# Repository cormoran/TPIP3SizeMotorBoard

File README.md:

# TPIP3SizeMotorBoard
ArduinoUnoCompatible Board for four wheel robot control (with TPIP3 image board)

[Document](https://cormoran.github.io/TPIP3SizeMotorBoard/)

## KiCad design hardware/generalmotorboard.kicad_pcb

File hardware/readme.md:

# 2016年度４号機向け モータ制御回路

## 機能

* ４つのモータを正転、逆転、停止、空転、速度調整
* ２つのサーボモータを制御
* 赤外線LED, 受信機
* 温度センサー
* 状態表示用LED 2つ
* VCC,GND出力付きアナログ入力対応汎用ポート 4つ （ガスセンサ等を接続可能）
* 汎用ディジタルIOポート 4つ（二つはスイッチとポート兼用）
* スイッチ入力 4つ（２つはIOポート兼用）
* Groveポート(I2C)
* シリアル通信ポート
* バッテリー電圧監視
* USBシリアル変換IC搭載、Arduino DEIによる書き込み対応
* USB給電・バッテリー給電自動切り替え（バッテリー優先）

など

一応2016年度 3号機向けだが、部内ロボコン等にも使用できるように色々付けてある

## 形状

* TPIP3の金属部分と完全に同じ大きさに設計
* ポートは全て横向きに設置することで高さを削減

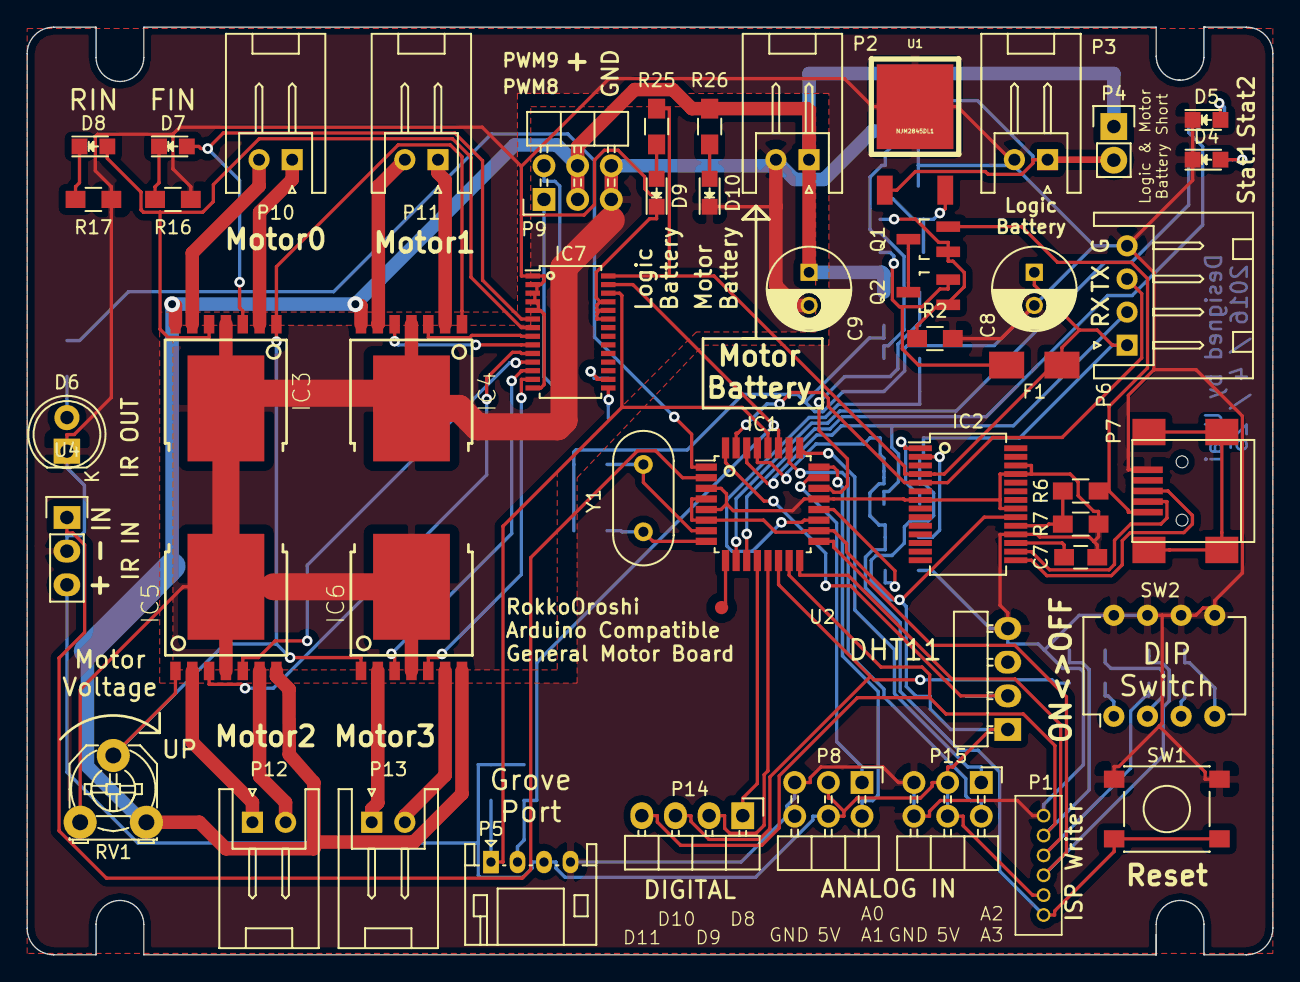
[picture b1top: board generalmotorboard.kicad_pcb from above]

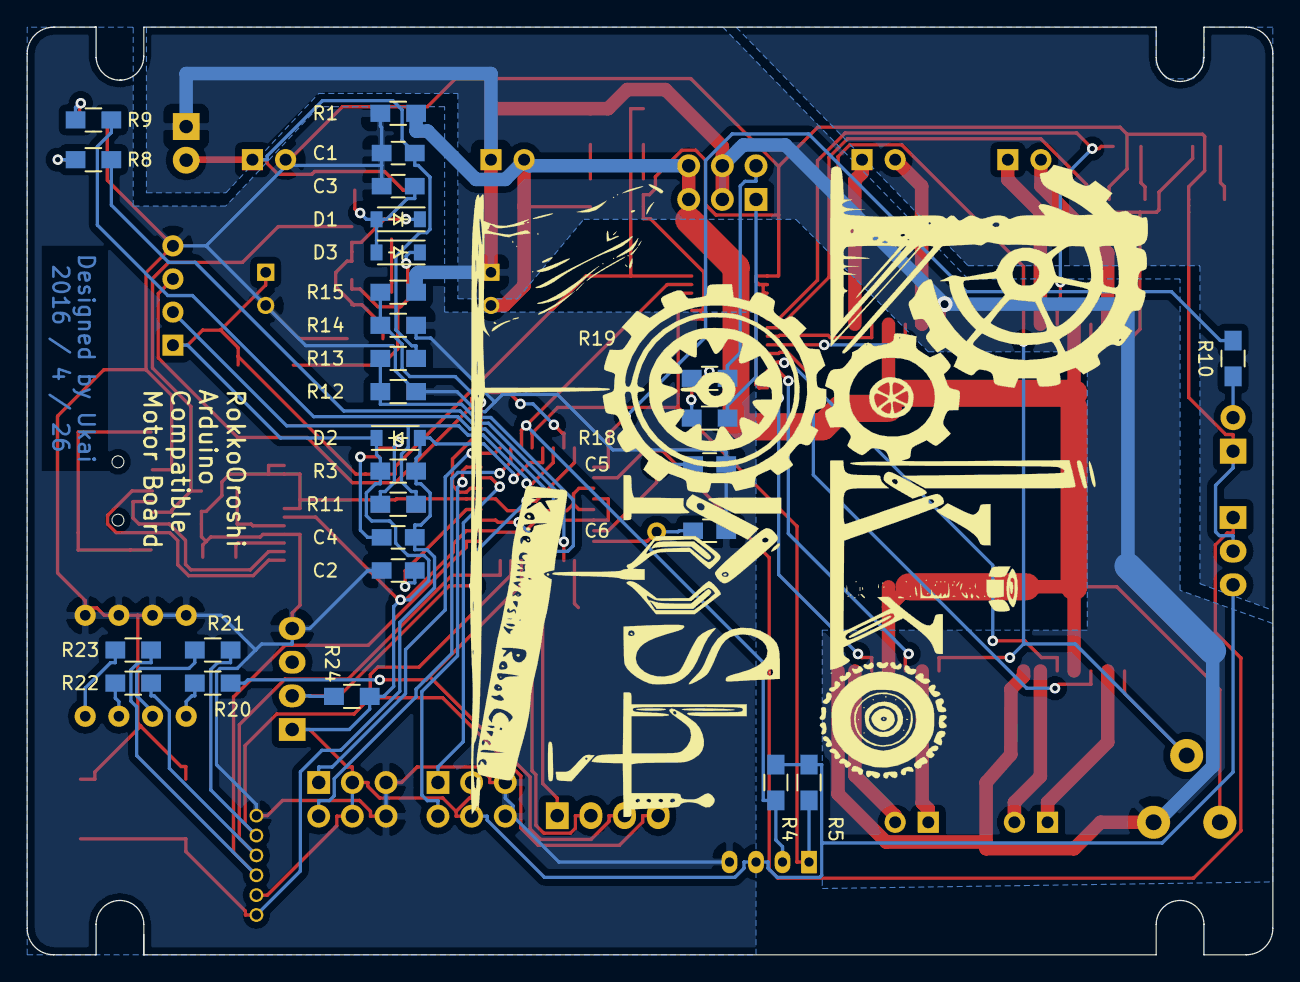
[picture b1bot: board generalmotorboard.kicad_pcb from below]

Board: 2 copper layers, 94.0 x 70.0 mm, 78 parts (28 on the bottom side), 74 nets.

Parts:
C1: 0.33uF; C_0805_HandSoldering
C2, C7: 100nF; C_0805_HandSoldering
C3: 2.2uF; C_0805_HandSoldering
C4: 0.1uF; C_0805_HandSoldering
C5, C6: 22pF; C_0805_HandSoldering
C8, C9: 470uF; C_Radial_D6.3_L11.2_P2.5
D1, D2, D3: D; SOD-123
D4: LED GREEN; LED_0805
D5: LED RED; LED_0805
D6: LED IR; LED-5MM
D7: Led FIN; LED_0805
D8: Led RIN; LED_0805
D9: Led MBAT; LED_0805
D10: Led LBAT; LED_0805
F1: 500mA; Fuse_SMD1206_HandSoldering
IC1: ATMEGA328P-A; TQFP-32_7x7mm_Pitch0.8mm
IC2: FT232RL; SSOP-28_5.3x10.2mm_Pitch0.65mm
IC3, IC4, IC5, IC6: BD6222HFP; HRP7
IC7: PCA9685_TSSOP-28_4MM; TSSOP-28_4.4x9.7mm_Pitch0.65mm
P1: ISP Writer; B6B-ZR
P2: MOTOR-BAT; JST_XH_S2B-XH-A_02x2.50mm_Angled
P3: LOGIC-BAT; JST_XH_S2B-XH-A_02x2.50mm_Angled
P4: JUMP; Pin_Header_Straight_1x02
P5: Grove; JST_PH_S4B-PH-K_04x2.00mm_Angled
P6: Serial; JST_XH_S4B-XH-A_04x2.50mm_Angled
P7: USB_OTG; USB_Mini-B
P8, P15: IO; Pin_Header_Angled_2x03_without_pin_show
P9: SERVO; Pin_Header_Angled_2x03_without_pin_show
P10: Motor1; JST_XH_S2B-XH-A_02x2.50mm_Angled
P11: Motor2; JST_XH_S2B-XH-A_02x2.50mm_Angled
P12: Motor3; JST_XH_S2B-XH-A_02x2.50mm_Angled
P13: Motor4; JST_XH_S2B-XH-A_02x2.50mm_Angled
P14: IO; Pin_Header_Angled_1x04_without_pin_show
P16: IOPAD; Fiducial_Mark
Q1, Q2: Q_PMOS_GSD; SOT-23_Handsoldering
R1: 0; R_0805_HandSoldering
R2, R3, R7, R13, R15, R24: 10k; R_0805_HandSoldering
R4, R5, R6, R20, R21, R22, R23: 4.7k; R_0805_HandSoldering
R8, R9, R16, R17, R25, R26: 470; R_0805_HandSoldering
R10, R18, R19: 330; R_0805_HandSoldering
R11: 1k; R_0805_HandSoldering
R12: 20k; R_0805_HandSoldering
R14: 30k; R_0805_HandSoldering
RV1: 10k; Potentiometer_Triwood_RM-065
SW1: SW_PUSH; SW_SPST_PTS645
SW2: SETTING; DIP-8_W7.62mm
U1: NJM2845DL1; TO-252-3
U2: DHT11
U4: IR_Receiver; Pin_Header_Straight_1x03
Y1: 16MHz; HC-49V

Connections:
5VBATSENS: IC1.19, R12.2, R13.1
8VBATSENS: IC1.22, R14.2, R15.1
+5V: C8.1, D2.1, F1.2, IC1.4, IC1.6, IC1.18, IC2.4, IC2.20, IC7.28, P1.2, P5.3, P6.1, P8.3, P8.4, P15.3, P15.4, R3.1, R4.1, R5.1, R24.1, R25.2, U2.1, U4.3
+8V: C9.1, IC3.7, IC4.7, IC5.7, IC6.7, P2.1, P4.1, P9.3, P9.4, R14.1, R26.2, RV1.3
A0: IC1.23, P8.1
A1: IC1.24, P8.2
A2: IC1.25, P15.1
A3: IC1.26, P15.2
BATTERY: C1.1, P3.1, P4.2, R12.1, U1.1
D8: IC1.12, P14.1
D9: IC1.13, P14.2
D10: IC1.14, P14.3, R20.1
D11: IC1.15, P1.5, P14.4, R21.1
DTR: C4.2, IC2.2
GND: C9.2, D10.1, IC3.4, IC3.P, IC4.4, IC4.P, IC5.4, IC5.P, IC6.4, IC6.P, P2.2, P9.5, P9.6, R1.1, RV1.1
GNDD: C1.2, C2.2, C3.2, C5.1, C6.1, C7.2, C8.2, D4.1, D5.1, D6.1, D9.1, IC1.3, IC1.5, IC1.21, IC2.7, IC2.18, IC2.21, IC2.25, IC2.26, IC7.1, IC7.2, IC7.3, IC7.4, IC7.5, IC7.14, IC7.23, IC7.24, IC7.25, P1.6, P3.2, P5.4, P6.4, P7.5, P8.5, P8.6, P15.5, P15.6, R1.2, R2.2, R7.2, R13.2, R15.2, R16.1, R17.1, SW1.1, SW2.5, SW2.6, SW2.7, SW2.8, U1.2, U2.4, U4.2
IR-RCV: IC1.2, U4.1
IRLED: IC1.1, R10.2
MISO: IC1.16, P1.4, R22.1
unnamed: C2.1, IC1.20
unnamed: C3.1, D1.2, D3.2, U1.3
unnamed: C5.2, IC1.7, Y1.1
unnamed: C6.2, IC1.8, Y1.2
unnamed: C7.1, IC2.17
unnamed: D1.1, Q1.1, Q2.1, R2.1
unnamed: D3.1, F1.1, Q2.2
unnamed: D4.2, R8.1
unnamed: D5.2, R9.1
unnamed: D6.2, R10.1
unnamed: D7.1, R16.2
unnamed: D7.2, IC3.3, IC7.6
unnamed: D8.1, R17.2
unnamed: D8.2, IC3.5, IC7.7
unnamed: D9.2, R25.1
unnamed: D10.2, R26.1
unnamed: IC1.9, P16.1
unnamed: IC2.1, R11.2
unnamed: IC2.15, P7.3
unnamed: IC2.16, P7.2
unnamed: IC2.19, R6.1, R7.1
unnamed: IC3.1, IC4.1, IC5.1, IC6.1, RV1.2
unnamed: IC3.2, P10.1
unnamed: IC3.6, P10.2
unnamed: IC4.2, P11.1
unnamed: IC4.3, IC7.8
unnamed: IC4.5, IC7.9
unnamed: IC4.6, P11.2
unnamed: IC5.2, P12.1
unnamed: IC5.3, IC7.10
unnamed: IC5.5, IC7.11
unnamed: IC5.6, P12.2
unnamed: IC6.2, P13.1
unnamed: IC6.3, IC7.12
unnamed: IC6.5, IC7.13
unnamed: IC6.6, P13.2
unnamed: P9.1, R18.1
unnamed: P9.2, R19.1
unnamed: Q1.3, Q2.3
unnamed: R20.2, SW2.1
unnamed: R21.2, SW2.2
unnamed: R22.2, SW2.3
unnamed: R23.2, SW2.4
PWM8: IC7.15, R18.2
PWM9: IC7.16, R19.2
RESET: C4.1, D2.2, IC1.29, P1.1, R3.2, SW1.2
RX: IC1.30, P6.2, R11.1
SCK: IC1.17, P1.3, R23.1
SCL: IC1.28, IC7.26, P5.1, R5.2
SDA: IC1.27, IC7.27, P5.2, R4.2
STAT1: IC1.10, R8.2
STAT2: IC1.11, R9.2
TEMP_SENSOR: IC1.32, R24.2, U2.2
TX: IC1.31, IC2.5, P6.3
USBVCC: P7.1, Q1.2, R6.2

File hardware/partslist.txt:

*代用表記は初回制作時の部品在庫に合わせたもの

# 抵抗

（チップ2012サイズ）
R1	0（半田ブリッジで良い）
R2	10k
R3	10k
R4	4.7k
R5	4.7k
R6	4.7k
R7	10k
R8	470
R9	470
R10	330

R11	1k
R12	20k
R13	10k
R14	30k
R15	10k
R16	470
R17	470
R18	330
R19	330
R20	4.7k

R21	4.7k
R22	4.7k
R23	4.7k
R24	10k
R25	470
R26	470

（半固定抵抗）
RV1	10k

# コンデンサ 

（チップ2012サイズ）
C1	0.33uF (0.47uFで代用)
C2	100nF
C3	2.2uF
C4	0.1uF
C5	22pF (15pFで代用)
C6	22pF (15pFで代用)
C7	100nF

(電解コンデンサ)
C8	470uF
C9	470uF

# ダイオード

D1	D
D2	D
D3	D

# LED

(チップ2012サイズ)
D4	LED GREEN（緑）
D5	LED RED（赤）
D7	Led FIN（任意）
D8	Led RIN（任意）
D9	Led MBAT（赤）
D10	Led LBAT（赤）

（砲弾型φ5mm）
D6	LED IR

# FET

Q1	Q_PMOS_GSD
Q2	Q_PMOS_GSD

# IC類
IC1	ATMEGA328P-A	メインマイコン
IC2	FT232RL 	USBシリアル変換IC
IC3	BD6222HFP	モータドライバ
IC4	BD6222HFP
IC5	BD6222HFP
IC6	BD6222HFP
IC7	PCA9685 	PWM出力IC
U1	NJM2845DL1	電圧変換用
U2	DHT11   	温度センサー
U4	IR_Receiver

# コネクタ

P1	ZHコネクタ	ISP Writer
P2	XHコネクタ	MOTOR-BAT
P3	XHコネクタ	LOGIC-BAT
P4	ピンヘッダ	JUMP
P5	Groveコネクタ	Grove
P6	XHコネクタ	Serial
P7	Mini-USBメス	USB_OTG
P8	ピンヘッダ横	IO
P9	ピンヘッダ横	SERVO
P10	XHコネクタ	Motor0
P11	XHコネクタ	Motor1
P12	XHコネクタ	Motor2
P13	XHコネクタ	Motor3
P14	ピンヘッダ横	IO
P15	ピンヘッダ横	IO
P16	（なし）	IOPAD

# スイッチ

SW1	タクトスイッチ	SW_PUSH
SW2	DIPスイッチ	SETTING

# その他

Y1	16MHz水晶発振子
F1	ポリスイッチ500mA

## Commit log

2016-05-15 基板画像等追加
2016-05-15 ライブラリ・サンプル等（まだ一部のみ）追加
2017-02-04 fix install script
2017-02-04 add document (gitbook)
2017-02-04 add comipled book
2017-02-04 rename
2017-02-05 remove external library
2017-02-05 add link to github
2017-02-05 リンクなど追加
2017-02-05 update gitbook
2017-02-05 modify sample
2017-02-05 move files
2017-02-05 add ir example
2017-02-05 add robot example(not complately work)
2017-02-05 update document
2017-02-05 update doc
